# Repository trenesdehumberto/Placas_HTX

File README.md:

# Placas HTX
Electrónica para control de maquetas ferroviarias.

Aqui podrá encontrar diferentes diseños electrónicos para controlar su maqueta ferroviaria. Estas placas hacen uso de Arduino y del bus LocoNet

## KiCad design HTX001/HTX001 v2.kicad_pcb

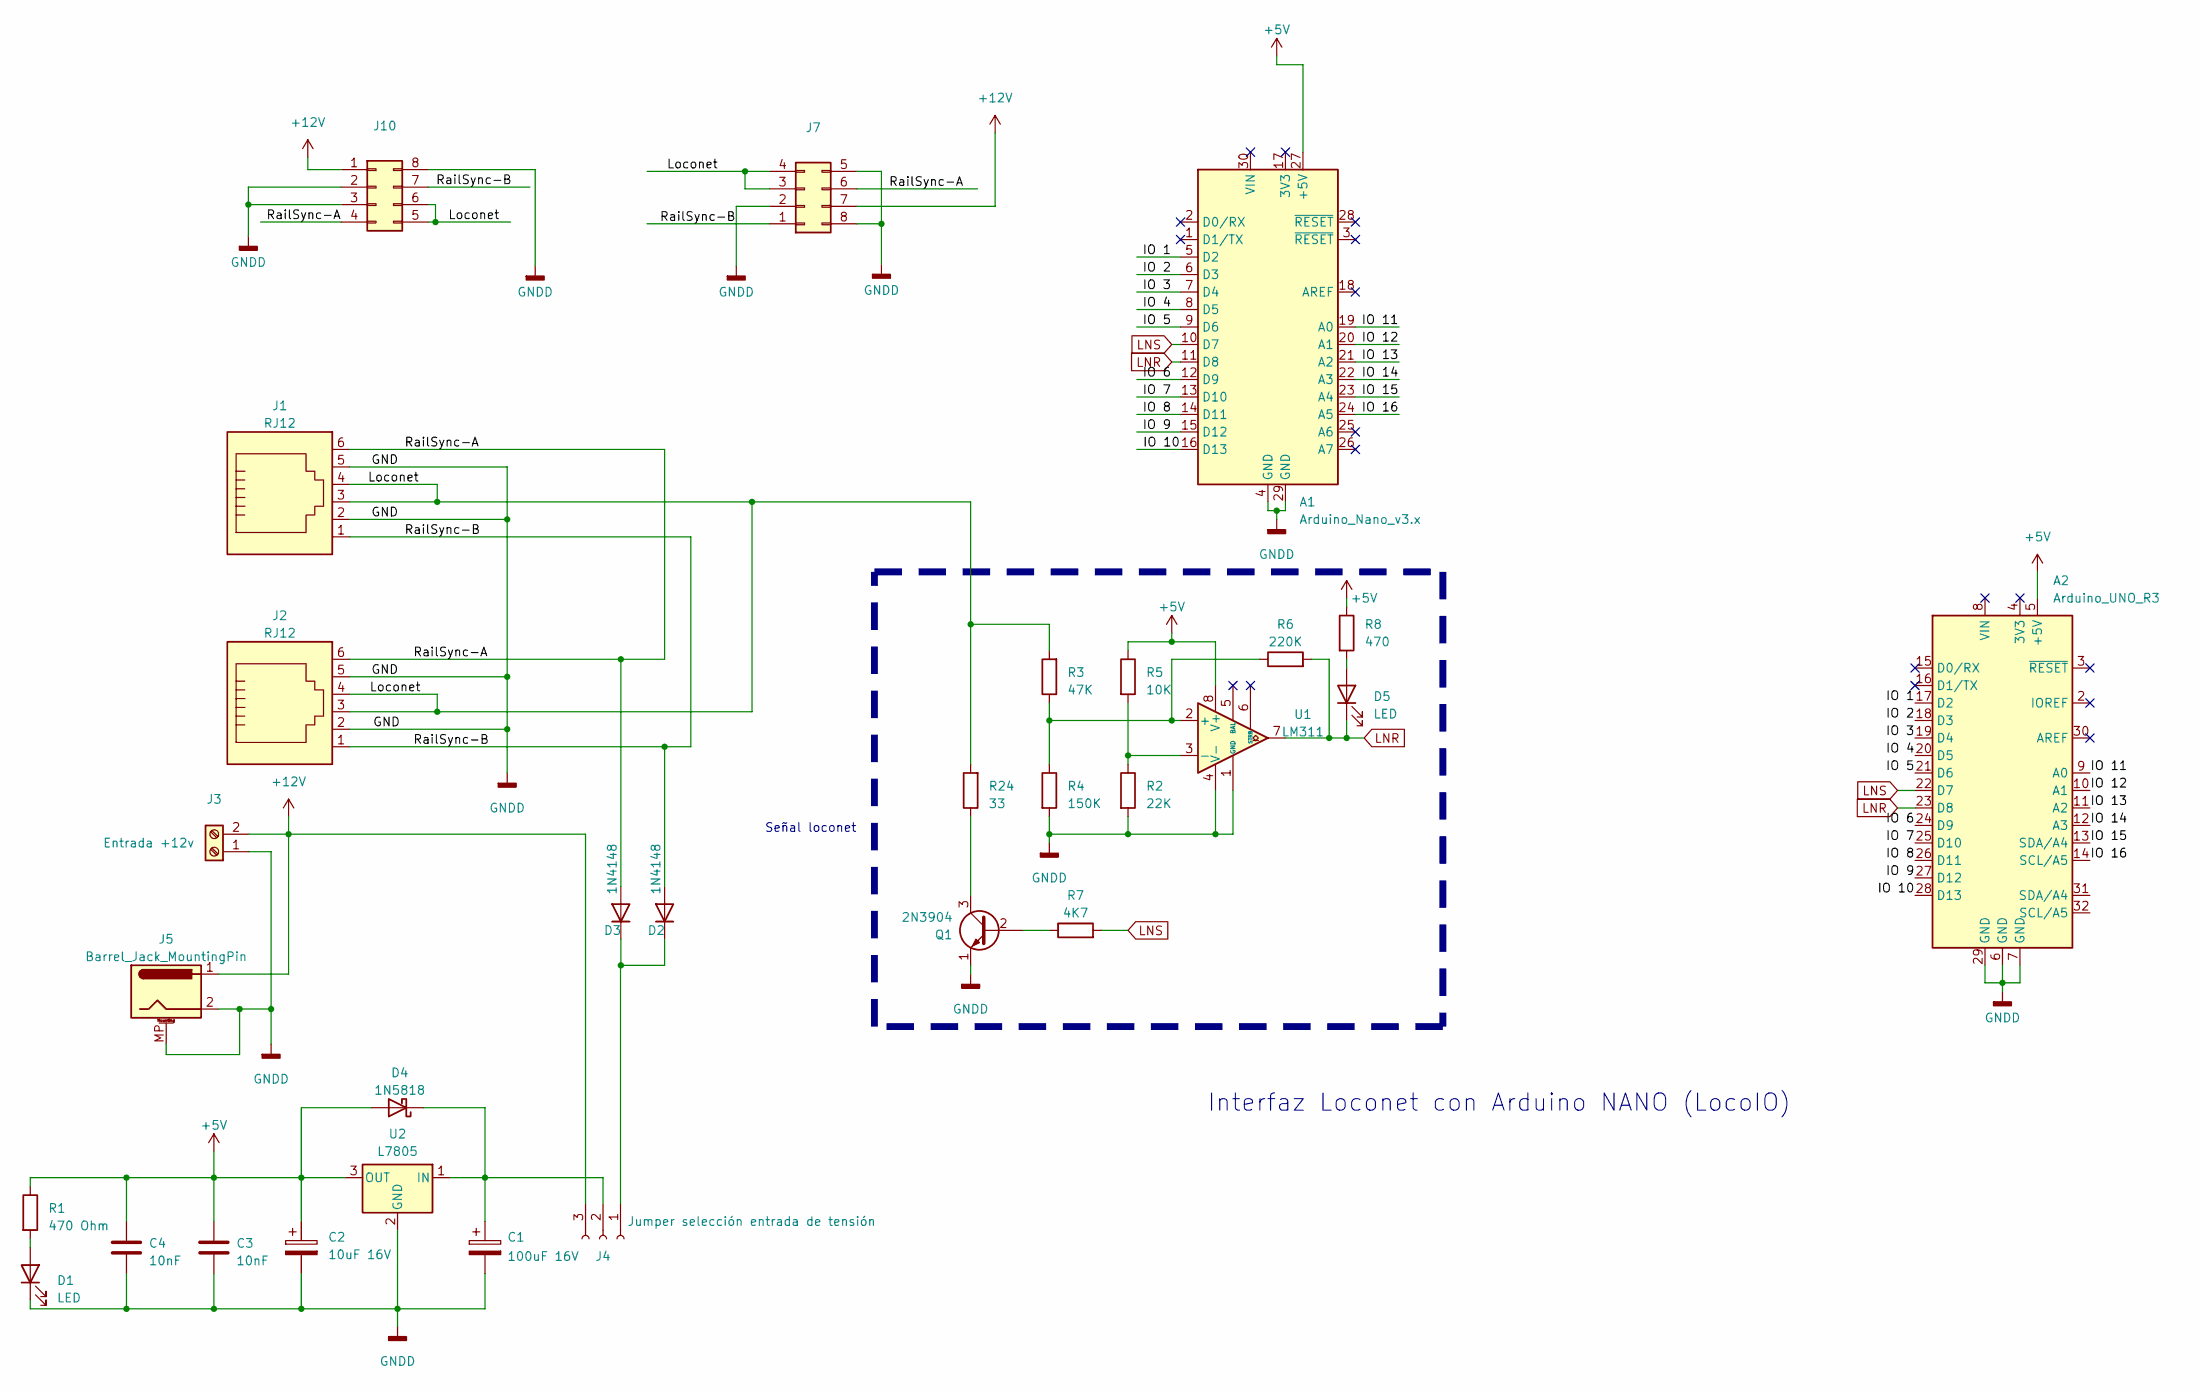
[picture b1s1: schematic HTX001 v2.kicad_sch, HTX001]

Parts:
A1: Arduino_Nano_v3.x; Arduino_Nano
A2: Arduino_UNO_R3
C1: 100uF 16V; CP_Radial_D5.0mm_P2.00mm
C2: 10uF 16V; CP_Radial_D5.0mm_P2.00mm
C3, C4: 10nF; C_Disc_D7.5mm_W2.5mm_P5.00mm
D1, D5: LED; LED_D3.0mm
D2, D3: 1N4148; D_DO-35_SOD27_P7.62mm_Horizontal
D4: 1N5818; D_DO-41_SOD81_P10.16mm_Horizontal
J1, J2: RJ12; RJ12_Amphenol_54601
J3: Entrada +12v; TerminalBlock_RND_205-00001_1x02_P5.00mm_Horizontal
J4: Jumper selección entrada de tensión; PinHeader_1x03_P2.54mm_Vertical
J5: Barrel_Jack_MountingPin; BarrelJack_GCT_DCJ200-10-A_Horizontal
J7, J10: Conn_02x04_Counter_Clockwise; PinSocket_2x04_P2.54mm_Horizontal
Q1: 2N3904; TO-92_Inline_Wide
R1: 470 Ohm; R_Axial_DIN0204_L3.6mm_D1.6mm_P7.62mm_Horizontal
R2: 22K; R_Axial_DIN0204_L3.6mm_D1.6mm_P7.62mm_Horizontal
R3: 47K; R_Axial_DIN0204_L3.6mm_D1.6mm_P7.62mm_Horizontal
R4: 150K; R_Axial_DIN0204_L3.6mm_D1.6mm_P7.62mm_Horizontal
R5: 10K; R_Axial_DIN0204_L3.6mm_D1.6mm_P7.62mm_Horizontal
R6: 220K; R_Axial_DIN0204_L3.6mm_D1.6mm_P7.62mm_Horizontal
R7: 4K7; R_Axial_DIN0204_L3.6mm_D1.6mm_P7.62mm_Horizontal
R8: 470; R_Axial_DIN0204_L3.6mm_D1.6mm_P7.62mm_Horizontal
R24: 33; R_Axial_DIN0204_L3.6mm_D1.6mm_P7.62mm_Horizontal
U1: LM311; DIP-8_W7.62mm_Socket
U2: L7805; TO-220-3_Horizontal_TabDown

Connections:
+5V: A1.27 (+5V), A2.5 (+5V), C2.1, C3.1, C4.1, D4.2 (A), R1.1, R5.1, R8.1, U1.8 (V+), U2.3 (OUT)
+12V: J3.2, J4.3, J5.1, J7.7, J10.1
/IO 1: A1.5 (D2), A2.17 (D2)
/IO 2: A1.6 (D3), A2.18 (D3)
/IO 3: A1.7 (D4), A2.19 (D4)
/IO 4: A1.8 (D5), A2.20 (D5)
/IO 5: A1.9 (D6), A2.21 (D6)
/IO 6: A1.12 (D9), A2.24 (D9)
/IO 7: A1.13 (D10), A2.25 (D10)
/IO 8: A1.14 (D11), A2.26 (D11)
/IO 9: A1.15 (D12), A2.27 (D12)
/IO 10: A1.16 (D13), A2.28 (D13)
/IO 11: A1.19 (A0), A2.9 (A0)
/IO 12: A1.20 (A1), A2.10 (A1)
/IO 13: A1.21 (A2), A2.11 (A2)
/IO 14: A1.22 (A3), A2.12 (A3)
/IO 15: A1.23 (A4), A2.13 (SDA/A4)
/IO 16: A1.24 (A5), A2.14 (SCL/A5)
/Loconet: J1.3, J1.4, J2.3, J2.4, J7.3, J7.4, J10.5, J10.6, R3.2, R24.2
/RailSync-A: D3.2 (A), J1.6, J2.6, J7.6, J10.4
/RailSync-B: D2.2 (A), J1.1, J2.1, J7.1, J10.7
GNDD: A1.4 (GND), A1.29 (GND), A2.6 (GND), A2.7 (GND), A2.29 (GND), C1.2, C2.2, C3.2, C4.2, D1.1 (K), J1.2, J1.5, J2.2, J2.5, J3.1, J5.2, J5.MP (MountPin), J7.2, J7.5, J7.8, J10.2, J10.3, J10.8, Q1.1 (E), R2.2, R4.2, U1.1 (GND), U1.4 (V-), U2.2 (GND)
LNR: A1.11 (D8), A2.23 (D8), D5.1 (K), R6.2, U1.7
LNS: A1.10 (D7), A2.22 (D7), R7.2
unnamed: D1.2 (A), R1.2
unnamed: D2.1 (K), D3.1 (K), J4.1
unnamed: C1.1, D4.1 (K), J4.2, U2.1 (IN)
unnamed: D5.2 (A), R8.2
unnamed: Q1.2 (B), R7.1
unnamed: Q1.3 (C), R24.1
unnamed: R3.1, R4.1, R6.1, U1.2 (+)
unnamed: R2.1, R5.2, U1.3 (-)

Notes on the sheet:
Interfaz Loconet con Arduino NANO (LocoIO)
Señal loconet

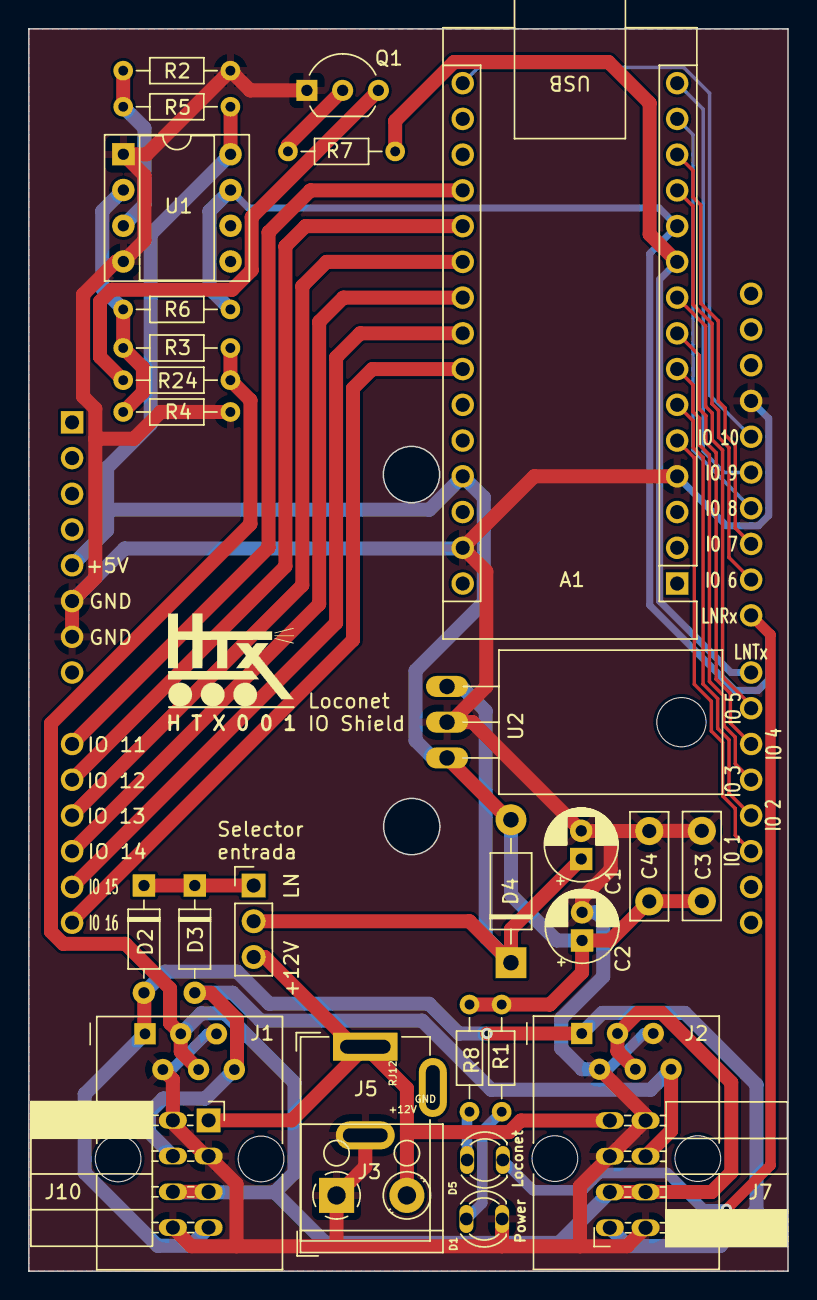
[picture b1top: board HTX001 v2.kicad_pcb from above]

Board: 2 copper layers, 53.9 x 88.3 mm, 30 parts (1 on the bottom side), 32 nets.

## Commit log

2023-02-23 Create HTX002
2024-04-25 Create HTX100
